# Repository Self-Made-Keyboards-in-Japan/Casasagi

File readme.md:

# Casasagi
The mechanical keyboard made by SMKiJ community.

Work in progress

## components library
need to install SMKiJ components library.
https://github.com/Self-Made-Keyboards-in-Japan/SMKiJ_keyboard

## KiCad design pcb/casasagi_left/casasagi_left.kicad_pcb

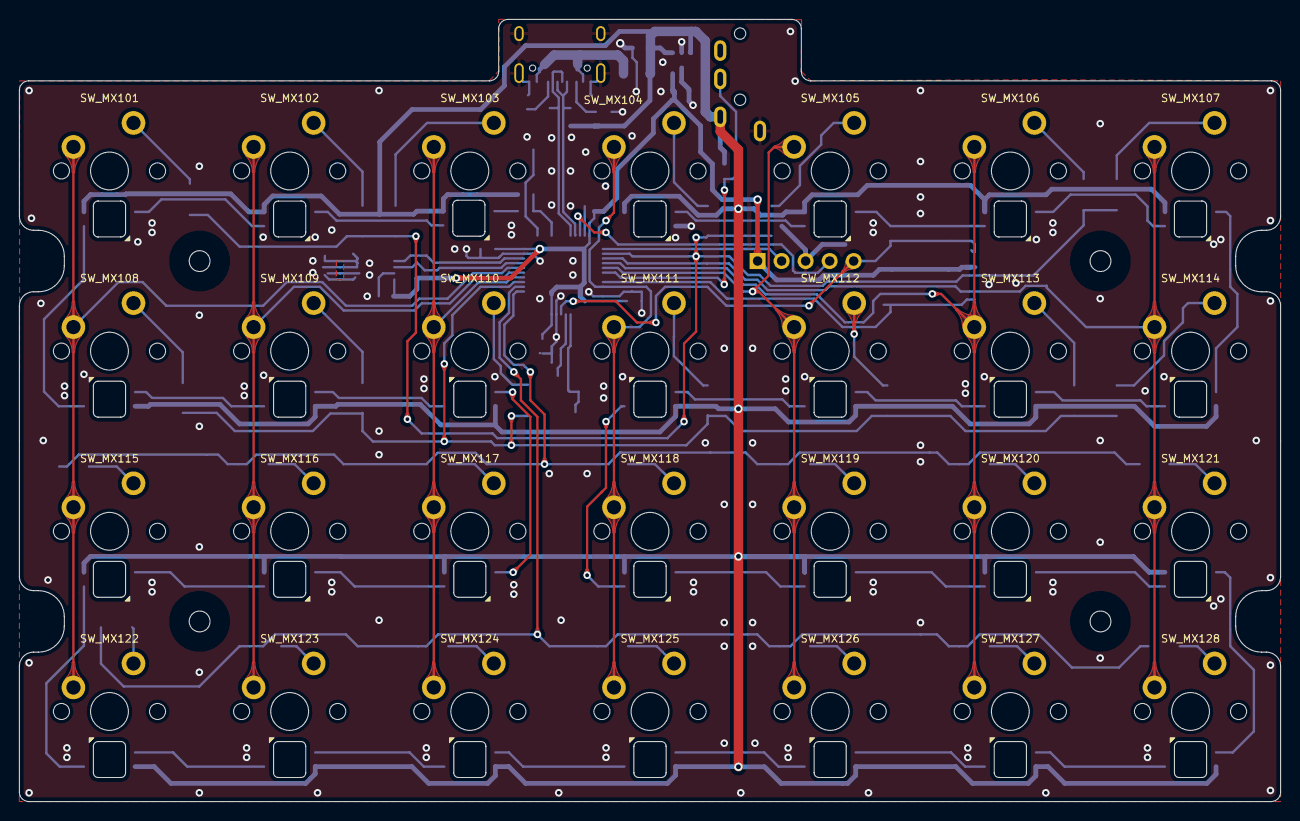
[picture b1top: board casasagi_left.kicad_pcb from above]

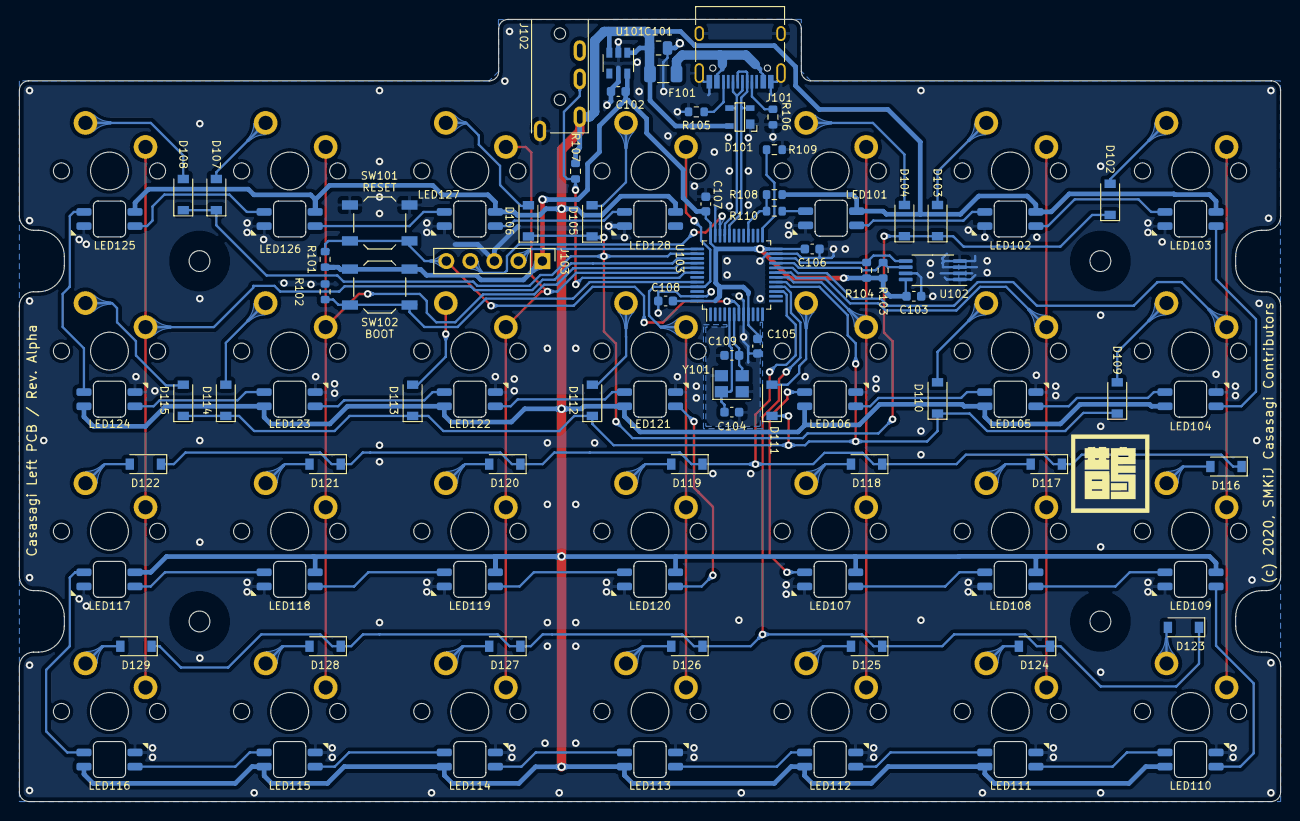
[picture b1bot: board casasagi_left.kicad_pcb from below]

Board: 2 copper layers, 133.3 x 82.7 mm, 119 parts (87 on the bottom side), 86 nets.

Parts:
C101: 10uF; C_0805_2012Metric
C102: 1uF; C_0603_1608Metric
C103, C105, C106, C107, C108: 0.1uF; C_0603_1608Metric
C104, C109: 22pF; C_0603_1608Metric
D101: PRTR5V0U2X; IC_SOT-143
D102, D103, D104, D105, D106, D107, D108, D109, D110, D111, D112, D113, D114, D115, D116, D117, D118, D119, D120, D121, D122, D123, D124, D125, D126, D127, D128, D129: 1N4148; D_SOD-123
F101: 1A; Fuse_1206_3216Metric
H1, H2, H3, H4: M2; MountingHole_2.2mm_M2
J101: USB_C_Receptacle_USB2.0; USB_C_Receptacle_HRO_TYPE-C-31-M-12
J102: AudioJack4; TRRS_MJ-4PP-9
J103: Conn_01x05; PinHeader_1x05_P2.54mm_Vertical
LED101, LED102, LED103, LED104, LED105, LED106, LED107, LED108, LED109, LED110, LED111, LED112, LED113, LED114, LED115, LED116, LED117, LED118, LED119, LED120, LED121, LED122, LED123, LED124, LED125, LED126, LED127, LED128: SK6812-MINI-E; LED_YS-SK6812MINI-E
LOGO1: Casasagi_logo; logo
R101, R102, R103, R104, R105, R106, R107, R108: 5.11k; R_0603_1608Metric
R109: DNP; R_0603_1608Metric
R110: 470R; R_0603_1608Metric
SW101: RESET; SW_SPST_TL3342
SW102: BOOT; SW_SPST_TL3342
SW_MX101, SW_MX102, SW_MX103, SW_MX104, SW_MX105, SW_MX106, SW_MX107, SW_MX108, SW_MX109, SW_MX110, SW_MX111, SW_MX112, SW_MX113, SW_MX114, SW_MX115, SW_MX116, SW_MX117, SW_MX118, SW_MX119, SW_MX120, SW_MX121, SW_MX122, SW_MX123, SW_MX124, SW_MX125, SW_MX126, SW_MX127, SW_MX128: SW_MX; SW_Cherry_MX_1.00u_PCB
U101: TLV73333PDBV; SOT-23-5
U102: AT24C256C-XHL-T; TSSOP-8_4.4x3mm_P0.65mm
U103: STM32F072C8Tx; LQFP-48_7x7mm_P0.5mm
Y101: 8MHz; Crystal_SMD_3225-4Pin_3.2x2.5mm

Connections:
+3V3: C102.2, C103.2, C105.2, C106.2, C107.2, C108.2, J103.1, R101.1, R103.1, R104.1, SW102.1, U101.5, U102.8, U103.9, U103.24, U103.36, U103.48
+5V: C101.2, D101.4, F101.1, J102.T, LED101.1, LED102.1, LED103.1, LED104.1, LED105.1, LED106.1, LED107.1, LED108.1, LED109.1, LED110.1, LED111.1, LED112.1, LED113.1, LED114.1, LED115.1, LED116.1, LED117.1, LED118.1, LED119.1, LED120.1, LED121.1, LED122.1, LED123.1, LED124.1, LED125.1, LED126.1, LED127.1, LED128.1, R107.1, R108.1, U101.1, U101.3
/COL0: SW_MX101.1, SW_MX108.1, SW_MX115.1, SW_MX122.1, U103.20
/COL1: SW_MX102.1, SW_MX109.1, SW_MX116.1, SW_MX123.1, U103.19
/COL2: SW_MX103.1, SW_MX110.1, SW_MX117.1, SW_MX124.1, U103.18
/COL3: SW_MX104.1, SW_MX111.1, SW_MX118.1, SW_MX125.1, U103.45
/COL4: SW_MX105.1, SW_MX112.1, SW_MX119.1, SW_MX126.1, U103.41
/COL5: SW_MX106.1, SW_MX113.1, SW_MX120.1, SW_MX127.1, U103.40
/COL6: SW_MX107.1, SW_MX114.1, SW_MX121.1, SW_MX128.1, U103.39
/I2C_SCL: R103.2, U102.6, U103.21
/I2C_SDA: R104.2, U102.5, U103.22
/LED: R108.2, R110.1, U103.28
/RESET: J103.5, R101.2, SW101.2, U103.7
/ROW0: D102.1, D103.1, D104.1, D105.1, D106.1, D107.1, D108.1, U103.38
/ROW1: D109.1, D110.1, D111.1, D112.1, D113.1, D114.1, D115.1, U103.17
/ROW2: D116.1, D117.1, D118.1, D119.1, D120.1, D121.1, D122.1, U103.15
/ROW3: D123.1, D124.1, D125.1, D126.1, D127.1, D128.1, D129.1, U103.16
/SPLIT_DATA: J102.R1, R107.2, U103.42
/SWCLK: J103.2, U103.37
/SWDIO: J103.4, U103.34
/USB_D+: D101.3, J101.A6, J101.B6, U103.33
/USB_D-: D101.2, J101.A7, J101.B7, U103.32
GND: C101.1, C102.1, C103.1, C104.2, C105.1, C106.1, C107.1, C108.1, C109.2, D101.1, J101.A1, J101.A12, J101.B1, J101.B12, J101.S1, J102.S, J103.3, LED101.3, LED102.3, LED103.3, LED104.3, LED105.3, LED106.3, LED107.3, LED108.3, LED109.3, LED110.3, LED111.3, LED112.3, LED113.3, LED114.3, LED115.3, LED116.3, LED117.3, LED118.3, LED119.3, LED120.3, LED121.3, LED122.3, LED123.3, LED124.3, LED125.3, LED126.3, LED127.3, LED128.3, R102.2, R105.2, R106.2, R109.2, SW101.1, U101.2, U102.1, U102.2, U102.3, U102.4, U102.7, U103.8, U103.23, U103.35, U103.47, Y101.2, Y101.4
unnamed: C104.1, U103.5, Y101.1
unnamed: C109.1, U103.6, Y101.3
unnamed: D102.2, SW_MX101.2
unnamed: D103.2, SW_MX102.2
unnamed: D104.2, SW_MX103.2
unnamed: D105.2, SW_MX104.2
unnamed: D106.2, SW_MX105.2
unnamed: D107.2, SW_MX106.2
unnamed: D108.2, SW_MX107.2
unnamed: D109.2, SW_MX108.2
unnamed: D110.2, SW_MX109.2
unnamed: D111.2, SW_MX110.2
unnamed: D112.2, SW_MX111.2
unnamed: D113.2, SW_MX112.2
unnamed: D114.2, SW_MX113.2
unnamed: D115.2, SW_MX114.2
unnamed: D116.2, SW_MX115.2
unnamed: D117.2, SW_MX116.2
unnamed: D118.2, SW_MX117.2
unnamed: D119.2, SW_MX118.2
unnamed: D120.2, SW_MX119.2
unnamed: D121.2, SW_MX120.2
unnamed: D122.2, SW_MX121.2
unnamed: D123.2, SW_MX122.2
unnamed: D124.2, SW_MX123.2
unnamed: D125.2, SW_MX124.2
unnamed: D126.2, SW_MX125.2
unnamed: D127.2, SW_MX126.2
unnamed: D128.2, SW_MX127.2
unnamed: D129.2, SW_MX128.2
unnamed: F101.2, J101.A4, J101.A9, J101.B4, J101.B9
unnamed: J101.A5, R106.1
unnamed: J101.B5, R105.1
unnamed: LED101.2, LED102.4
unnamed: LED101.4, R110.2
unnamed: LED102.2, LED103.4
unnamed: LED103.2, LED104.4
unnamed: LED104.2, LED105.4
unnamed: LED105.2, LED106.4
unnamed: LED106.2, LED107.4
unnamed: LED107.2, LED108.4
unnamed: LED108.2, LED109.4
unnamed: LED109.2, LED110.4
unnamed: LED110.2, LED111.4
unnamed: LED111.2, LED112.4
unnamed: LED112.2, LED113.4
unnamed: LED113.2, LED114.4
unnamed: LED114.2, LED115.4
unnamed: LED115.2, LED116.4
unnamed: LED116.2, LED117.4
unnamed: LED117.2, LED118.4
unnamed: LED118.2, LED119.4
unnamed: LED119.2, LED120.4
unnamed: LED120.2, LED121.4
unnamed: LED121.2, LED122.4
unnamed: LED122.2, LED123.4
unnamed: LED123.2, LED124.4
unnamed: LED124.2, LED125.4
unnamed: LED125.2, LED126.4
unnamed: LED126.2, LED127.4
unnamed: LED127.2, LED128.4
unnamed: R102.1, SW102.2, U103.44
unnamed: R109.1, U103.25

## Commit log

2020-11-03 1st commit
2020-11-03 add info about kicad library
2020-11-03 change pcb outline
2020-11-05 replace stm32f072 symbol to kicad pre-installed one
2020-11-07 Increase cutout size to make keyboard assemblable
2020-11-07 move dimension to comment layer
2020-11-08 correct tab and connectors dimention
2020-11-25 make switch matrix simple
2020-11-26 add handness resistor
2020-12-01 adjust traces and silks
2020-12-01 ignore _autosave*
2020-12-01 add casasagi right pcb
2020-12-01 update reference number for panelization
2020-12-01 add copyright on pcbs
2020-12-02 add teardrops to right pcb
2020-12-02 add teardrop and adjust trace
2020-12-02 fix directory name
2020-12-02 add logo!!!!
2020-12-03 add combined pcb
2020-12-03 add fiducial mark
2020-12-03 add schematic pdf
2020-12-10 prepare pcb for BOM and add BOM left
2020-12-11 add right BOM
2020-12-11 add production BOM
2020-12-12 update mousebite
2021-04-25 add rev.alpha production pcb
2021-05-02 Change boss thru hole to M2 thru hole
    Introduce M2 thru hole to fix switch plate and PCB together using M2 screw. Spacer style boss can be placed at the edge cutout.
2021-05-04 replace M2 holes to drill holes

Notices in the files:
pcb/casasagi_left/casasagi_left.kicad_pcb:
(c) 2020, SMKiJ Casasagi Contributors
